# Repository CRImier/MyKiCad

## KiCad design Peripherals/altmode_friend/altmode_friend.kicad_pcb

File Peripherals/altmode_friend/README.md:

# Altmode Friend

This is a castellated module with a RP2040 and a FUSB302B on it.
The idea is to ship this as a together with a MicroPython
library that helps you talk USB-C - whether it's to get altmodes
out of a port, or provide some altmodes to a device,
all within a comfortable high-level environment.

Main three uses are DisplayPort, making PD sources, and PD sinks,
but you can most certainly find more than that.
Many RP2040 GPIOs are broken out, so that you can toggle hardware
in response to PD messages, i.e. signal muxes, or power management stuff.

Bring your own 3.3V. You don't need much else though!

The RP2040's USB port is broken out on the header. There's also
a voltage divider (with Zener fp) from VBUS. FUSB's VBUS is not wired up -
you might not want to do it either; due to some mfg weirdness,
it's a very sensitive pin, and not connecting it does not impact
FUSB's operation in any way. Two extra ADC pins are broken out,
but one of them is connected to BOOT with a resistor, so you need
to remove/shift the resistor marked "BT>" before you can use it.

VCONN is jumpered to on-module 3.3V by default. If emarkers don't work,
remove/shift the jumper and provide idk like 5V or whatever.
The jumper is marked as "<VC". It's important that you remove it.

The module is 2.54mm pitch, 6 pins on all sides. There's no footprint yet.
That said, all pins are on 2.54mm grid, can't be hard to add it wherever you want it.

This board can be used as a building block of your own board
or it can be used standalone, or copy-pasted as a heart of a new design,
Whichever path you take, I hope this board helps you.

## Notes

- Pin headers are arranged in a way that this board can be plugged into a breadboard.
- Signal names are silkscreened on the board's bottom layer.
- This board is untested and there's no guarantees of fitness.
- I recommend a stencil for assembling this board.

## Info

- Software: Kicad 6
- Version: 1
- PCB size: 18x18mm
- Layer count: 2

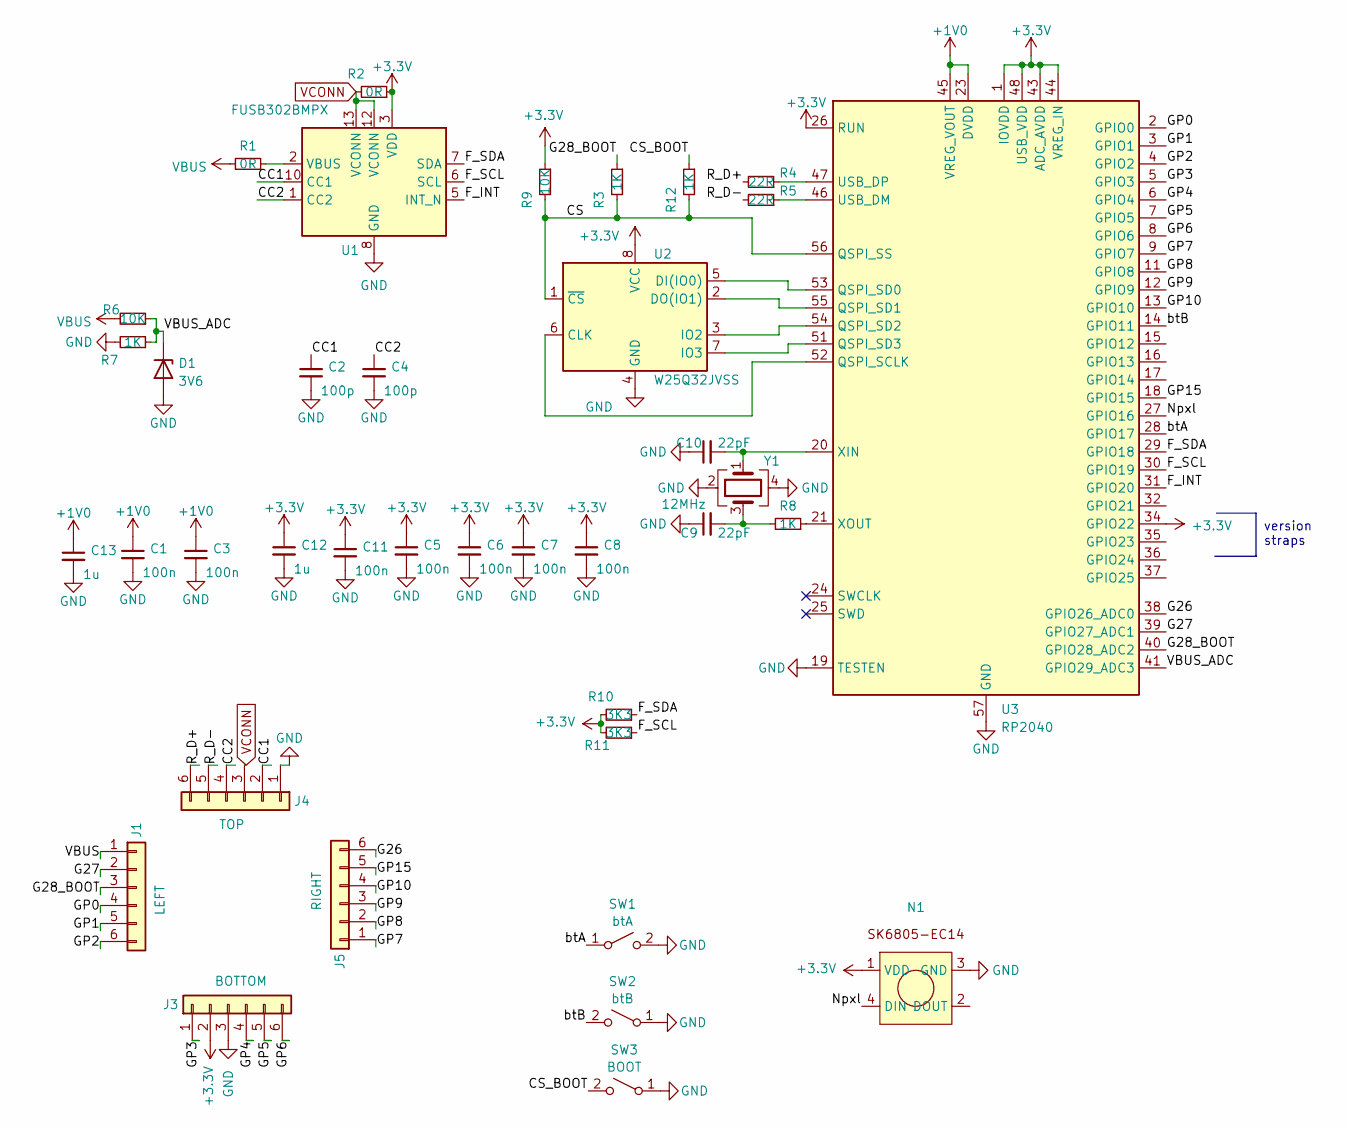
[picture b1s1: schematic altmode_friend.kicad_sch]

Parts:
C1, C3, C5, C6, C7, C8, C11: 100n; C_0402_1005Metric
C2, C4: 100p; C_0603_1608Metric
C9, C10: 22pF; C_0603_1608Metric
C12, C13: 1u; C_0402_1005Metric
D1: 3V6; D_0805_2012Metric
J1: LEFT; 6p_header
J3: BOTTOM; 6p_header
J4: TOP; 6p_header
J5: RIGHT; 6p_header
N1: SK6805-EC14
R1: 0R; R_0402_1005Metric
R2: 0R; R_0603_1608Metric
R3, R7, R8, R12: 1K; R_0402_1005Metric
R4, R5: 22R; R_0402_1005Metric
R6, R9: 10K; R_0402_1005Metric
R10, R11: 3K3; R_0402_1005Metric
SW1: btA; SW-SMD_4P-L2.8-W1.9-P1.20-LS3.0
SW2: btB; SW-SMD_4P-L2.8-W1.9-P1.20-LS3.0
SW3: BOOT; SW-SMD_4P-L2.8-W1.9-P1.20-LS3.0
U1: FUSB302BMPX; WQFN-14-1EP_2.5x2.5mm_P0.5mm_EP1.45x1.45mm
U2: W25Q32JVSS; DFN-8-1EP_3x2mm_P0.5mm_EP1.3x1.5mm
U3: RP2040; QFN-56-1EP_7x7mm_P0.4mm_EP3.2x3.2mm
Y1: 12MHz; Crystal_SMD_3225-4Pin_3.2x2.5mm

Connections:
+1V0: C1.1, C3.1, C13.1, U3.23 (DVDD), U3.45 (VREG_VOUT), U3.50 (DVDD)
+3.3V: C5.1, C6.1, C7.1, C8.1, C11.1, C12.1, J3.2, N1.1 (VDD), R2.1, R9.1, R10.2, R11.2, U1.3 (VDD), U1.4 (VDD), U2.8 (VCC), U3.1 (IOVDD), U3.10 (IOVDD), U3.22 (IOVDD), U3.26 (RUN), U3.33 (IOVDD), U3.34 (GPIO22), U3.42 (IOVDD), U3.43 (ADC_AVDD), U3.44 (VREG_IN), U3.48 (USB_VDD), U3.49 (IOVDD)
/CC1: C2.1, J4.2, U1.10 (CC1), U1.11 (CC1)
/CC2: C4.1, J4.4, U1.1 (CC2), U1.14 (CC2)
/CS: R3.2, R9.2, R12.2, U2.1 (~CS), U3.56 (QSPI_SS)
/CS_BOOT: R12.1, SW3.2 (B)
/F_INT: U1.5 (INT_N), U3.31 (GPIO20)
/F_SCL: R11.1, U1.6 (SCL), U3.30 (GPIO19)
/F_SDA: R10.1, U1.7 (SDA), U3.29 (GPIO18)
/G26: J5.6, U3.38 (GPIO26_ADC0)
/G27: J1.2, U3.39 (GPIO27_ADC1)
/G28_BOOT: J1.3, R3.1, U3.40 (GPIO28_ADC2)
/GP0: J1.4, U3.2 (GPIO0)
/GP1: J1.5, U3.3 (GPIO1)
/GP2: J1.6, U3.4 (GPIO2)
/GP3: J3.1, U3.5 (GPIO3)
/GP4: J3.4, U3.6 (GPIO4)
/GP5: J3.5, U3.7 (GPIO5)
/GP6: J3.6, U3.8 (GPIO6)
/GP7: J5.1, U3.9 (GPIO7)
/GP8: J5.2, U3.11 (GPIO8)
/GP9: J5.3, U3.12 (GPIO9)
/GP10: J5.4, U3.13 (GPIO10)
/GP15: J5.5, U3.18 (GPIO15)
/Npxl: N1.4 (DIN), U3.27 (GPIO16)
/R_D+: J4.6, R4.2
/R_D-: J4.5, R5.2
/VBUS_ADC: D1.1 (K), R6.1, R7.1, U3.41 (GPIO29_ADC3)
/btA: SW1.1 (A), U3.28 (GPIO17)
/btB: SW2.2 (B), U3.14 (GPIO11)
GND: C1.2, C2.2, C3.2, C4.2, C5.2, C6.2, C7.2, C8.2, C9.1, C10.1, C11.2, C12.2, C13.2, D1.2 (A), J3.3, J4.1, N1.3 (GND), R7.2, SW1.2 (B), SW2.1 (A), SW3.1 (A), U1.8 (GND), U1.9 (GND), U1.15 (GND), U2.4 (GND), U3.19 (TESTEN), U3.57 (GND), Y1.2, Y1.4
unnamed: C9.2, R8.2, Y1.3
unnamed: R1.1, U1.2 (VBUS)
unnamed: U2.6 (CLK), U3.52 (QSPI_SCLK)
unnamed: U2.5 (DI(IO0)), U3.53 (QSPI_SD0)
unnamed: U2.2 (DO(IO1)), U3.55 (QSPI_SD1)
unnamed: U2.3 (IO2), U3.54 (QSPI_SD2)
unnamed: U2.7 (IO3), U3.51 (QSPI_SD3)
unnamed: R5.1, U3.46 (USB_DM)
unnamed: R4.1, U3.47 (USB_DP)
unnamed: C10.2, U3.20 (XIN), Y1.1
unnamed: R8.1, U3.21 (XOUT)
VBUS: J1.1, R1.2, R6.2
VCONN: J4.3, R2.2, U1.12 (VCONN), U1.13 (VCONN)

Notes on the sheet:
version straps

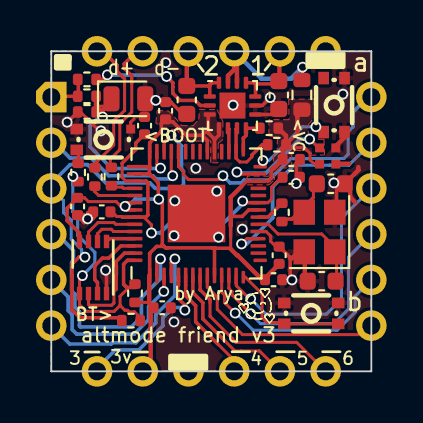
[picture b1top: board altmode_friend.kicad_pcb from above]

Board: 2 copper layers, 17.8 x 17.8 mm, 38 parts (0 on the bottom side), 44 nets.

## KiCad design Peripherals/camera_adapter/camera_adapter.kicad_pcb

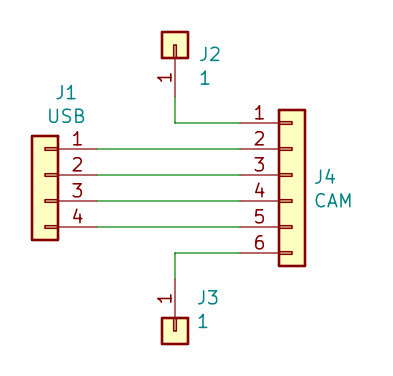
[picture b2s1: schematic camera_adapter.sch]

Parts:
J1: USB; PinHeader_1x04_P2.00mm_Vertical
J2, J3: 1; PinHeader_1x01_P2.00mm_Vertical
J4: CAM; JST_SH_BM06B-SRSS-TB_1x06-1MP_P1.00mm_Vertical

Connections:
unnamed: J1.1, J4.2
unnamed: J1.2, J4.3
unnamed: J1.3, J4.4
unnamed: J1.4, J4.5
unnamed: J2.1, J4.1
unnamed: J3.1, J4.6

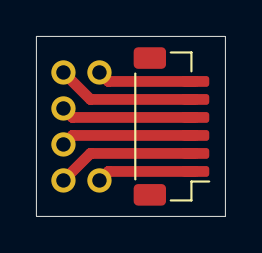
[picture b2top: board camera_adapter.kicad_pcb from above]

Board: 2 copper layers, 10.5 x 10.0 mm, 4 parts (0 on the bottom side), 6 nets.

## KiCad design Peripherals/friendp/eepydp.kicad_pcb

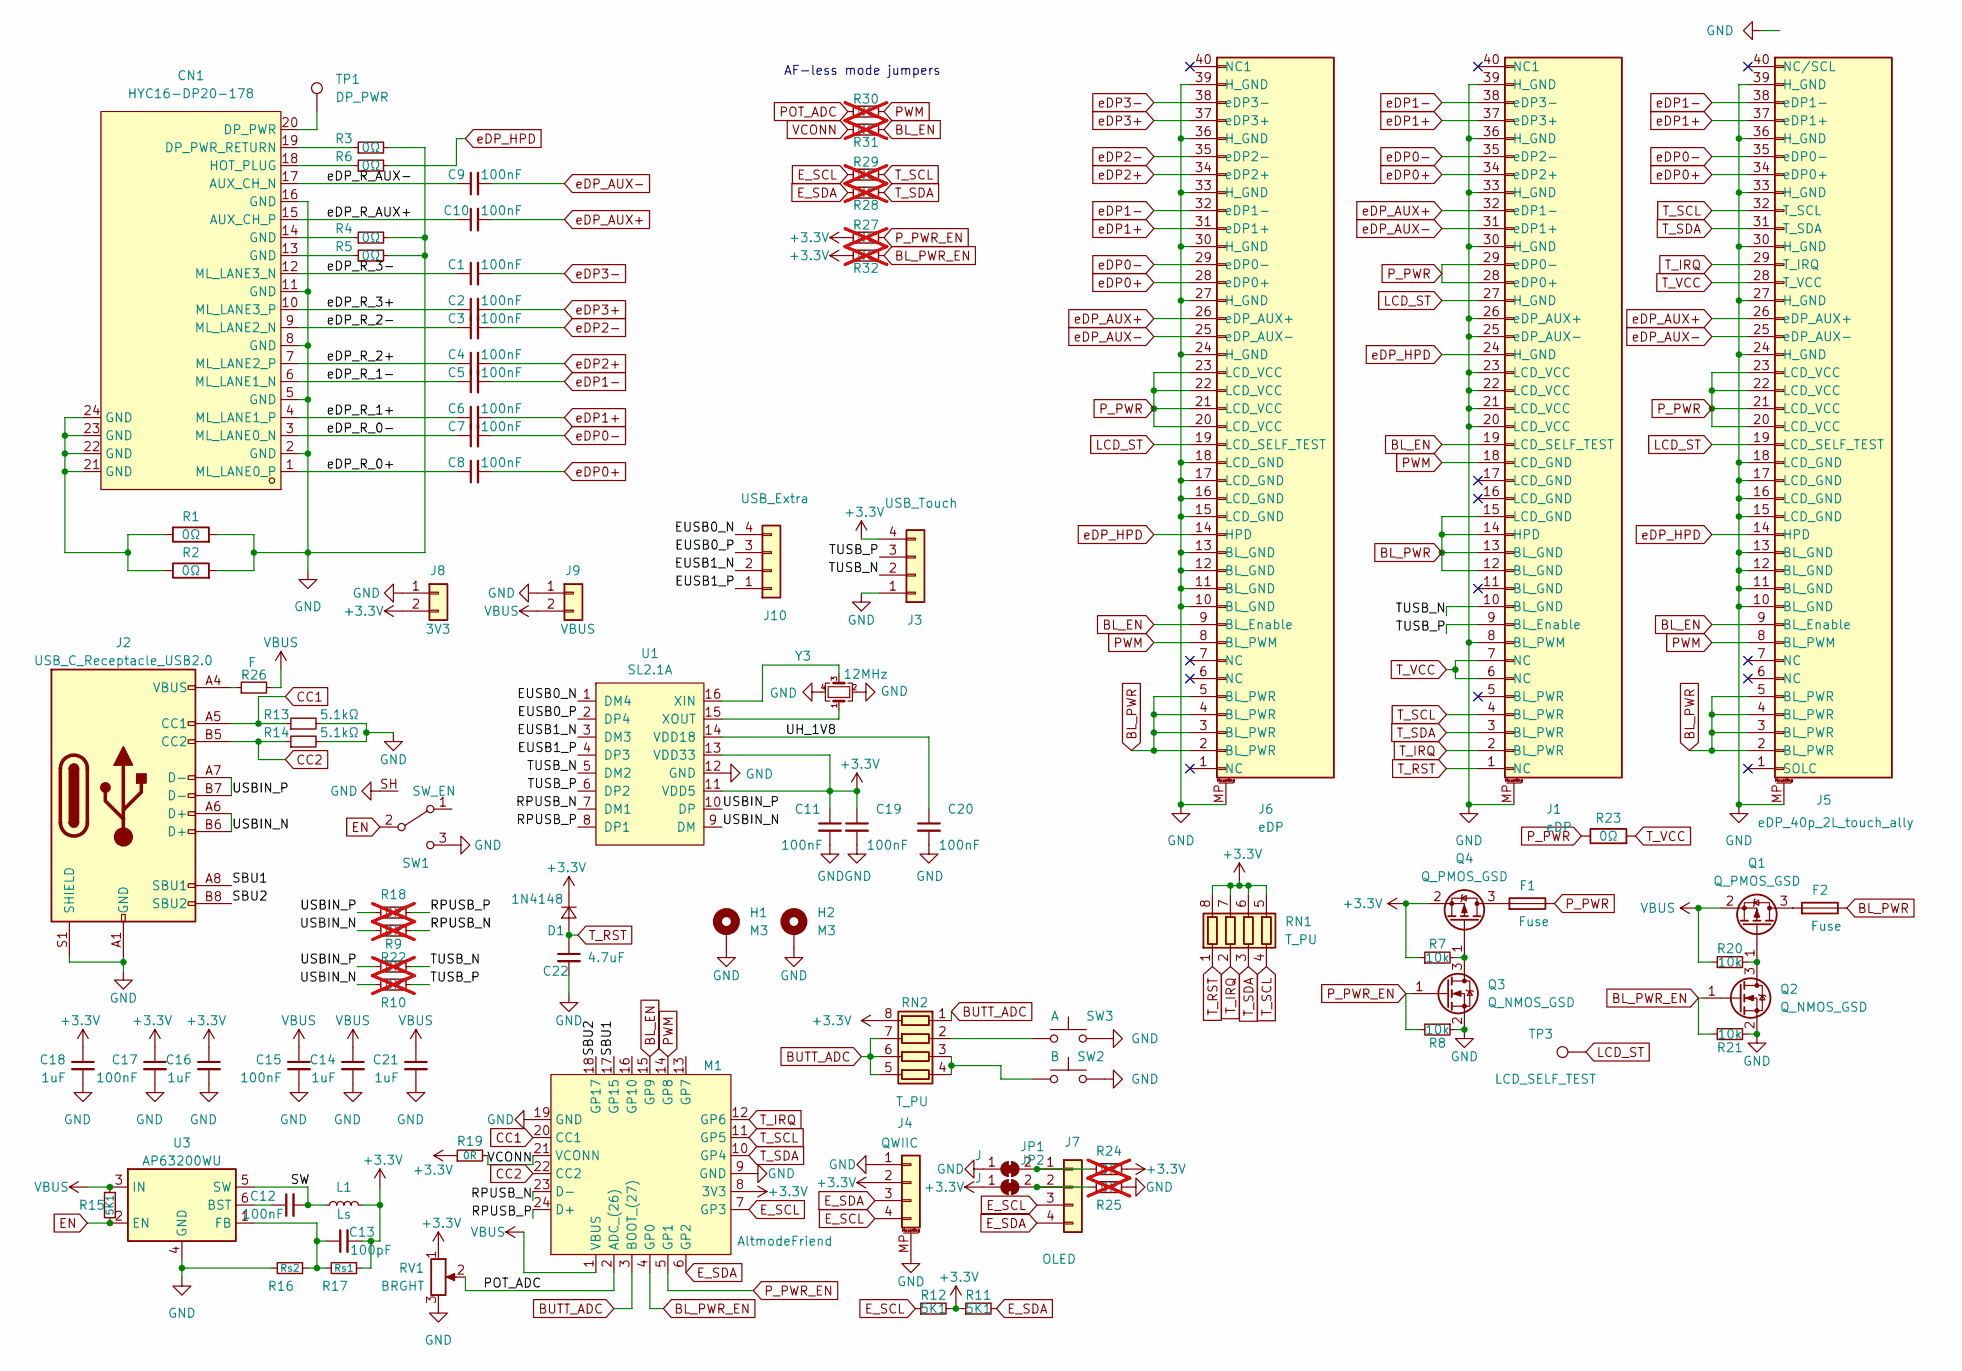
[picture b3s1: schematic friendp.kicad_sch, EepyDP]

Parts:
C1, C2, C3, C4, C5, C6, C7, C8, C9, C10: 100nF; C_0402_1005Metric
C11, C12, C17, C19, C20: 100nF; C_0603_1608Metric
C13: 100pF; C_0603_1608Metric
C14, C16, C18, C21: 1uF; C_0805_2012Metric
C15: 100nF; C_0805_2012Metric
C22: 4.7uF; C_0805_2012Metric
CN1: HYC16-DP20-178; DP-SMD_HYC16-DP20-178; LCSC Part C711350
D1: 1N4148; D_SOD-123F
F1, F2: Fuse; Fuse_0805_2012Metric
H1, H2: M3; MountingHole_3.2mm_M3_Pad
J1, J6: eDP; TE_4-1734839-0_1x40-1MP_P0.5mm_Horizontal
J2: USB_C_Receptacle_USB2.0; USB_C_Receptacle_HRO_TYPE-C-31-M-12
J3: USB_Touch; PinHeader_1x04_P2.54mm_Vertical
J4: QWIIC; JST_SH_SM04B-SRSS-TB_1x04-1MP_P1.00mm_Horizontal
J5: eDP_40p_2L_touch_ally; TE_4-1734839-0_1x40-1MP_P0.5mm_Horizontal
J7: OLED; PinHeader_1x04_P2.54mm_Vertical
J8: 3V3; PinHeader_1x02_P2.54mm_Vertical
J9: VBUS; PinHeader_1x02_P2.54mm_Vertical
J10: USB_Extra; PinHeader_1x04_P2.54mm_Vertical
JP1, JP2: J; R_0603_1608Metric_Jumper
L1: Ls; L_Bourns-SRN4018
M1: AltmodeFriend; altmode_friend
Q1, Q4: Q_PMOS_GSD; SOT-23
Q2, Q3: Q_NMOS_GSD; SOT-23
R1, R2: 0Ω; R_0603_1608Metric
R3, R4, R5, R6, R23: 0Ω; R_0603_1608Metric_Jumper
R7, R8, R20, R21: 10k; R_0603_1608Metric
R9, R10, R18, R22, R24, R25: 0R; R_0603_1608Metric; not fitted
R11, R12, R15: 5K1; R_0603_1608Metric
R13, R14: 5.1kΩ; R_0603_1608Metric
R16: Rs2; R_0603_1608Metric
R17: Rs1; R_0603_1608Metric
R19: 0R; R_0603_1608Metric_Jumper
R26: F; R_0805_2012Metric
R27, R28, R29, R30, R31, R32: NC; R_0603_1608Metric; not fitted
RN1, RN2: T_PU; R_Array_Convex_4x0603
RV1: BRGHT; RES-ADJ-TH_VZ067TL1B202
SW1: SW_EN; SW_SPDT_PCM12_SH
SW2: B; SW_SPST_FSMSM
SW3: A; SW_SPST_FSMSM
TP1: DP_PWR; TestPoint_Pad_1.0x1.0mm
TP3: LCD_SELF_TEST; TestPoint_Pad_1.0x1.0mm
U1: SL2.1A; SO-16_3.9x9.9mm_P1.27mm
U3: AP63200WU; TSOT-23-6
Y3: 12MHz; Crystal_SMD_3225-4Pin_3.2x2.5mm

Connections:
+3.3V: C11.1, C13.2, C16.1, C17.1, C18.1, C19.1, D1.1 (K), J3.4, J4.2, J8.2, JP2.1 (A), L1.2, M1.8 (3V3), Q4.2 (S), R7.1, R11.1, R12.2, R17.1, R19.1, R24.1, R27.1, R32.1, RN1.5 (R4.2), RN1.6 (R3.2), RN1.7 (R2.2), RN1.8 (R1.2), RN2.8 (R1.2), RV1.1, U1.11 (VDD5), U1.13 (VDD33)
/EUSB0_N: J10.4, U1.1 (DM4)
/EUSB0_P: J10.3, U1.2 (DP4)
/EUSB1_N: J10.2, U1.3 (DM3)
/EUSB1_P: J10.1, U1.4 (DP3)
/RPUSB_N: M1.23 (D-), R22.1, U1.7 (DM1)
/RPUSB_P: M1.24 (D+), R18.1, U1.8 (DP1)
/SBU1: J2.A8 (SBU1), M1.17 (GP15)
/SBU2: J2.B8 (SBU2), M1.18 (GP17)
/SW: C12.2, L1.1, U3.5 (SW)
/TUSB_N: J1.10 (BL_GND), J3.2, R9.1, U1.5 (DM2)
/TUSB_P: J1.9 (BL_Enable), J3.3, R10.1, U1.6 (DP2)
/UH_1V8: C20.1, U1.14 (VDD18)
/USBIN_N: J2.A6 (D+), J2.B6 (D+), R10.2, R22.2, U1.9 (DM)
/USBIN_P: J2.A7 (D-), J2.B7 (D-), R9.2, R18.2, U1.10 (DP)
/eDP_R_0+: C8.1, CN1.1 (ML_LANE0_P)
/eDP_R_0-: C7.1, CN1.3 (ML_LANE0_N)
/eDP_R_1+: C6.1, CN1.4 (ML_LANE1_P)
/eDP_R_1-: C5.1, CN1.6 (ML_LANE1_N)
/eDP_R_2+: C4.1, CN1.7 (ML_LANE2_P)
/eDP_R_2-: C3.1, CN1.9 (ML_LANE2_N)
/eDP_R_3+: C2.1, CN1.10 (ML_LANE3_P)
/eDP_R_3-: C1.1, CN1.12 (ML_LANE3_N)
/eDP_R_AUX+: C10.1, CN1.15 (AUX_CH_P)
/eDP_R_AUX-: C9.1, CN1.17 (AUX_CH_N)
BL_EN: J1.19 (LCD_SELF_TEST), J5.9 (BL_Enable), J6.9 (BL_Enable), M1.15 (GP9), R31.2
BL_PWR: F2.1, J1.12 (BL_GND), J1.13 (BL_GND), J1.14 (HPD), J1.15 (LCD_GND), J5.2 (BL_PWR), J5.3 (BL_PWR), J5.4 (BL_PWR), J5.5 (BL_PWR), J6.2 (BL_PWR), J6.3 (BL_PWR), J6.4 (BL_PWR), J6.5 (BL_PWR)
BL_PWR_EN: M1.4 (GP0), Q2.1 (G), R21.2, R32.2
BUTT_ADC: M1.3 (BOOT_(27)), RN2.1 (R1.1), RN2.5 (R4.2), RN2.6 (R3.2), RN2.7 (R2.2)
CC1: J2.A5 (CC1), M1.20 (CC1), R13.1
CC2: J2.B5 (CC2), M1.22 (CC2), R14.1
EN: R15.1, SW1.2 (B), U3.2 (EN)
E_SCL: J4.4, J7.3, M1.7 (GP3), R12.1, R29.1
E_SDA: J4.3, J7.4, M1.6 (GP2), R11.2, R28.1
GND: C11.2, C14.2, C15.2, C16.2, C17.2, C18.2, C19.2, C20.2, C21.2, C22.2, CN1.2 (GND), CN1.5 (GND), CN1.8 (GND), CN1.11 (GND), CN1.16 (GND), H1.1, H2.1, J1.8 (BL_PWM), J1.20 (LCD_VCC), J1.21 (LCD_VCC), J1.22 (LCD_VCC), J1.23 (LCD_VCC), J1.25 (eDP_AUX-), J1.26 (eDP_AUX+), J1.30 (H_GND), J1.33 (H_GND), J1.36 (H_GND), J1.39 (H_GND), J1.MP, J2.A1 (GND), J2.A12 (GND), J2.B1 (GND), J2.B12 (GND), J2.S1 (SHIELD), J3.1, J4.1, J4.MP (MountPin), J5.10 (BL_GND), J5.11 (BL_GND), J5.12 (BL_GND), J5.13 (BL_GND), J5.15 (LCD_GND), J5.16 (LCD_GND), J5.17 (LCD_GND), J5.18 (LCD_GND), J5.24 (H_GND), J5.27 (H_GND), J5.30 (H_GND), J5.33 (H_GND), J5.36 (H_GND), J5.39 (H_GND), J5.MP, J6.10 (BL_GND), J6.11 (BL_GND), J6.12 (BL_GND), J6.13 (BL_GND), J6.15 (LCD_GND), J6.16 (LCD_GND), J6.17 (LCD_GND), J6.18 (LCD_GND), J6.24 (H_GND), J6.27 (H_GND), J6.30 (H_GND), J6.33 (H_GND), J6.36 (H_GND), J6.39 (H_GND), J6.MP, J8.1, J9.1, JP1.1 (A), M1.9 (GND), M1.19 (GND), Q2.2 (S), Q3.2 (S), R1.2, R2.2, R3.2, R4.2, R5.2, R8.1, R13.2, R14.2, R16.2, R21.1, R25.1, RV1.3, SW1.3 (C), SW1.SH, SW2.1, SW3.1, U1.12 (GND), U3.4 (GND), Y3.2, Y3.4
LCD_ST: J1.27 (H_GND), J5.19 (LCD_SELF_TEST), J6.19 (LCD_SELF_TEST), TP3.1
unnamed: CN1.20 (DP_PWR), TP1.1
unnamed: CN1.19 (DP_PWR_RETURN), R3.1
unnamed: CN1.13 (GND), R5.1
unnamed: CN1.14 (GND), R4.1
unnamed: CN1.21 (GND), CN1.22 (GND), CN1.23 (GND), CN1.24 (GND), R1.1, R2.1
unnamed: CN1.18 (HOT_PLUG), R6.1
unnamed: J2.A4 (VBUS), J2.A9 (VBUS), J2.B4 (VBUS), J2.B9 (VBUS), R26.1
unnamed: J7.1, JP1.2 (B), R24.2
unnamed: J7.2, JP2.2 (B), R25.2
unnamed: F2.2, Q1.3 (D)
unnamed: Q1.1 (G), Q2.3 (D), R20.2
unnamed: Q3.3 (D), Q4.1 (G), R7.2
unnamed: F1.2, Q4.3 (D)
unnamed: RN2.2 (R2.1), SW3.2
unnamed: RN2.3 (R3.1), RN2.4 (R4.1), SW2.2
unnamed: U1.16 (XIN), Y3.3
unnamed: U1.15 (XOUT), Y3.1
unnamed: C12.1, U3.6 (BST)
unnamed: C13.1, R16.1, R17.2, U3.1 (FB)
POT_ADC: M1.2 (ADC_(26)), R30.1, RV1.2
PWM: J1.18 (LCD_GND), J5.8 (BL_PWM), J6.8 (BL_PWM), M1.14 (GP8), R30.2
P_PWR: F1.1, J1.28 (eDP0+), J1.29 (eDP0-), J5.20 (LCD_VCC), J5.21 (LCD_VCC), J5.22 (LCD_VCC), J5.23 (LCD_VCC), J6.20 (LCD_VCC), J6.21 (LCD_VCC), J6.22 (LCD_VCC), J6.23 (LCD_VCC), R23.1
P_PWR_EN: M1.5 (GP1), Q3.1 (G), R8.2, R27.2
T_IRQ: J1.2 (BL_PWR), J5.29 (T_IRQ), M1.12 (GP6), RN1.2 (R2.1)
T_RST: C22.1, D1.2 (A), J1.1 (NC), RN1.1 (R1.1)
T_SCL: J1.4 (BL_PWR), J5.32 (T_SCL), M1.11 (GP5), R29.2, RN1.4 (R4.1)
T_SDA: J1.3 (BL_PWR), J5.31 (T_SDA), M1.10 (GP4), R28.2, RN1.3 (R3.1)
T_VCC: J1.6 (NC), J1.7 (NC), J5.28 (T_VCC), R23.2
VBUS: C14.1, C15.1, C21.1, J9.2, M1.1 (VBUS), Q1.2 (S), R15.2, R20.1, R26.2, U3.3 (IN)
VCONN: M1.21 (VCONN), R19.2, R31.1
eDP0+: C8.2, J1.34 (eDP2+), J5.34 (eDP0+), J6.28 (eDP0+)
eDP0-: C7.2, J1.35 (eDP2-), J5.35 (eDP0-), J6.29 (eDP0-)
eDP1+: C6.2, J1.37 (eDP3+), J5.37 (eDP1+), J6.31 (eDP1+)
eDP1-: C5.2, J1.38 (eDP3-), J5.38 (eDP1-), J6.32 (eDP1-)
eDP2+: C4.2, J6.34 (eDP2+)
eDP2-: C3.2, J6.35 (eDP2-)
eDP3+: C2.2, J6.37 (eDP3+)
eDP3-: C1.2, J6.38 (eDP3-)
eDP_AUX+: C10.2, J1.32 (eDP1-), J5.26 (eDP_AUX+), J6.26 (eDP_AUX+)
eDP_AUX-: C9.2, J1.31 (eDP1+), J5.25 (eDP_AUX-), J6.25 (eDP_AUX-)
eDP_HPD: J1.24 (H_GND), J5.14 (HPD), J6.14 (HPD), R6.2

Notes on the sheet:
AF-less mode jumpers

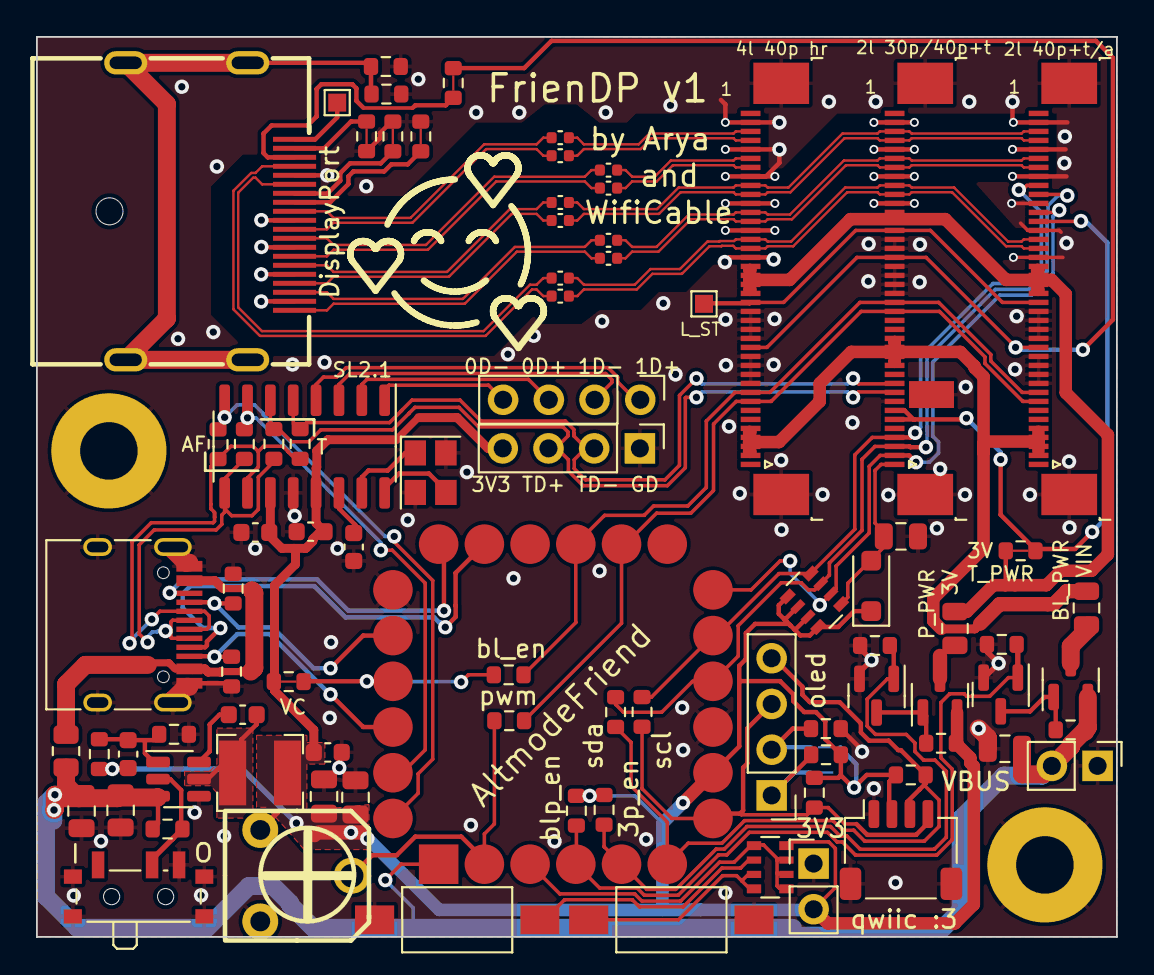
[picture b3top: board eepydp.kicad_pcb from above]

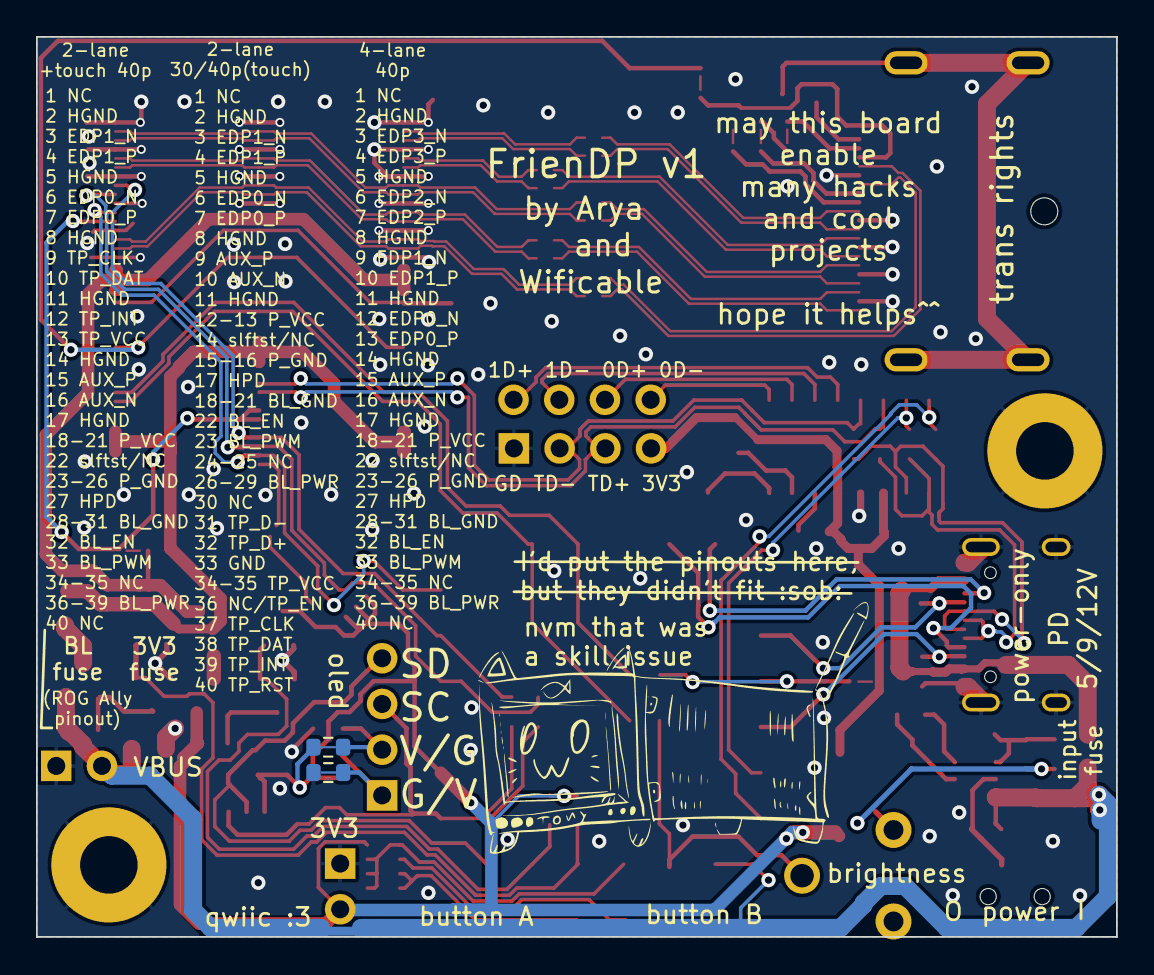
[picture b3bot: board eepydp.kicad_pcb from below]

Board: 4 copper layers, 60.0 x 50.0 mm, 89 parts (2 on the bottom side), 77 nets.

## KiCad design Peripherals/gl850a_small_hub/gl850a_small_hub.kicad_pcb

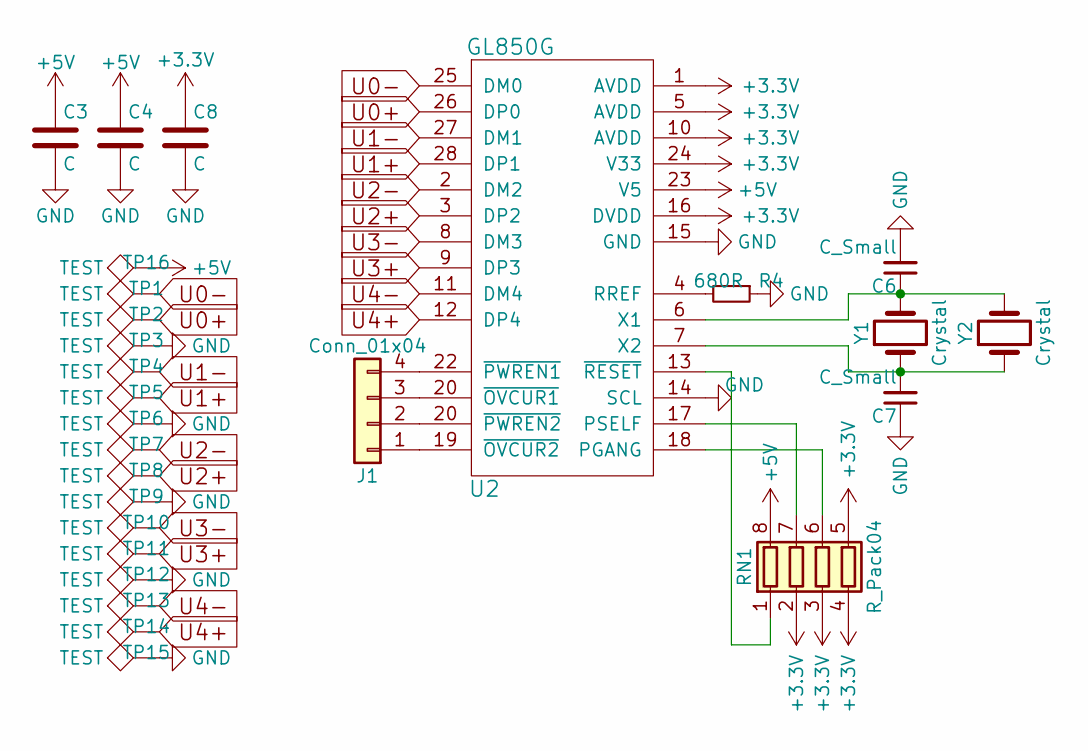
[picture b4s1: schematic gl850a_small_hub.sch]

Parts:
C3, C8: C; C_0603
C4: C; C_0805
C6, C7: C_Small; C_0603
J1: Conn_01x04; Pin_Header_Straight_1x04_Pitch1.27mm
R4: 680R; R_0603
RN1: R_Pack04; R_Array_Convex_4x0603
TP1, TP2, TP3, TP4, TP5, TP6, TP7, TP8, TP9, TP10, TP11, TP12, TP13, TP14, TP15, TP16: TEST; StrainReliefPoint
U2: GL850G; SSOP-28_3.9x9.9mm_Pitch0.635mm
Y1: Crystal; Crystal_SMD_3215-2pin_3.2x1.5mm
Y2: Crystal; Crystal_HC49-U_Vertical

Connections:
+3V3: C8.1, RN1.2 (R2.1), RN1.3 (R3.1), RN1.4 (R4.1), RN1.5 (R4.2), U2.1 (AVDD), U2.5 (AVDD), U2.10 (AVDD), U2.16 (DVDD), U2.24 (V33)
+5V: C3.1, C4.1, RN1.8 (R1.2), TP16.1, U2.23 (V5)
GND: C3.2, C4.2, C6.2, C7.1, C8.2, R4.1, TP3.1, TP6.1, TP9.1, TP12.1, TP15.1, U2.14 (SCL), U2.15 (GND)
unnamed: C6.1, U2.6 (X1), Y1.2, Y2.2
unnamed: C7.2, U2.7 (X2), Y1.1, Y2.1
unnamed: J1.1, U2.19 (~OVCUR2)
unnamed: J1.2, J1.3, U2.20 (~OVCUR1)
unnamed: J1.4, U2.22 (~PWREN1)
unnamed: R4.2, U2.4 (RREF)
unnamed: RN1.1 (R1.1), U2.13 (~RESET)
unnamed: RN1.6 (R3.2), U2.18 (PGANG)
unnamed: RN1.7 (R2.2), U2.17 (PSELF)
U0+: TP2.1, U2.26 (DP0)
U0-: TP1.1, U2.25 (DM0)
U1+: TP5.1, U2.28 (DP1)
U1-: TP4.1, U2.27 (DM1)
U2+: TP8.1, U2.3 (DP2)
U2-: TP7.1, U2.2 (DM2)
U3+: TP11.1, U2.9 (DP3)
U3-: TP10.1, U2.8 (DM3)
U4+: TP14.1, U2.12 (DP4)
U4-: TP13.1, U2.11 (DM4)

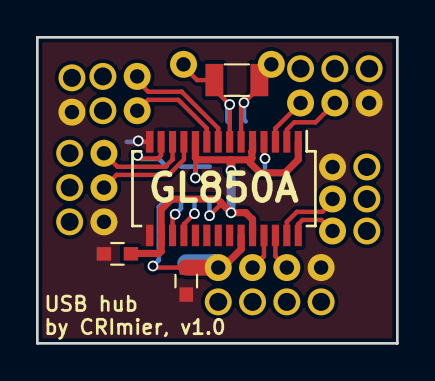
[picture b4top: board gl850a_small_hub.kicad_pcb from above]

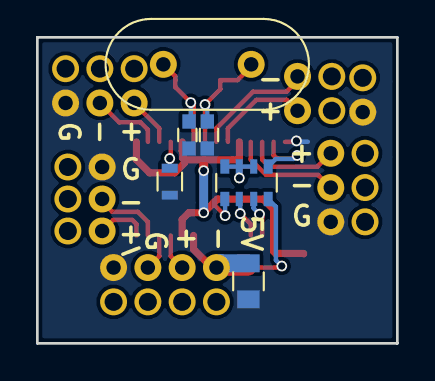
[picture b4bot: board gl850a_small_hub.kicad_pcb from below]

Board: 2 copper layers, 20.0 x 17.0 mm, 26 parts (6 on the bottom side), 19 nets.

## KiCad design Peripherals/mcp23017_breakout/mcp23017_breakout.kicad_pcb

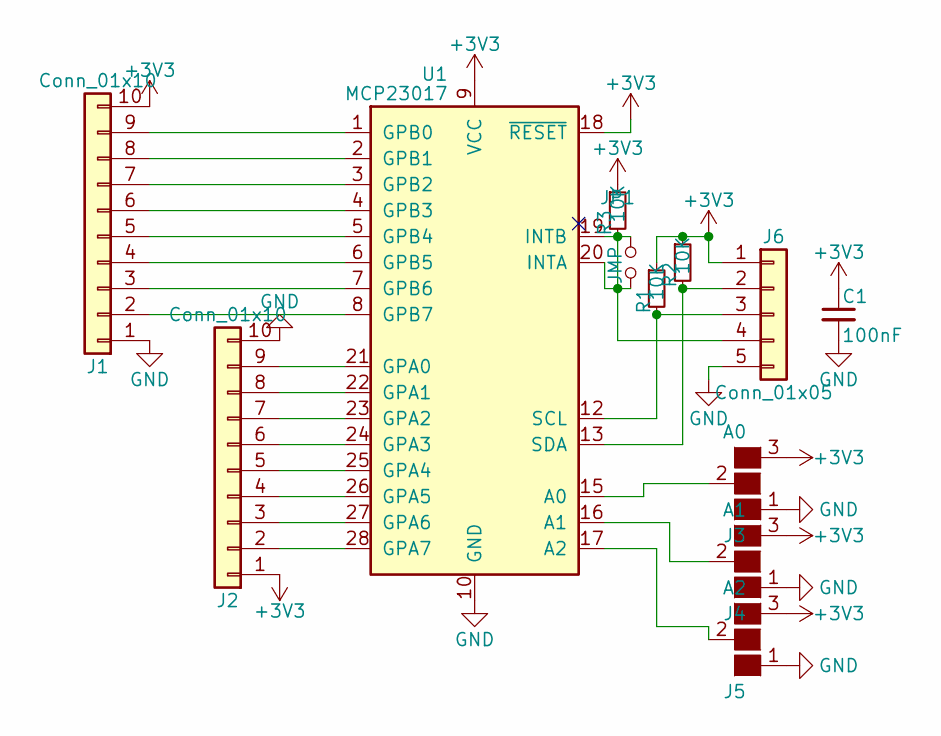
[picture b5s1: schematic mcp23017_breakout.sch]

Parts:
C1: 100nF; C_0805_HandSoldering
J1, J2: Conn_01x10; Pin_Header_Straight_1x10_Pitch2.54mm
J3: A0; GS3
J4: A1; GS3
J5: A2; GS3
J6: Conn_01x05; Pin_Header_Straight_1x05_Pitch2.54mm
JP1: JMP; GS2
R1, R2, R3: 10K; R_0805_HandSoldering
U1: MCP23017; SSOP-28_5.3x10.2mm_Pitch0.65mm

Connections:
+3V3: C1.1, J1.10, J2.1, J3.3 (G3), J4.3 (G3), J5.3 (G3), J6.1, R1.1, R2.1, R3.1, U1.9 (VCC), U1.18 (~RESET)
GND: C1.2, J1.1, J2.10, J3.1 (G1), J4.1 (G1), J5.1 (G1), J6.5, U1.10 (GND)
unnamed: J1.2, U1.8 (GPB7)
unnamed: J1.3, U1.7 (GPB6)
unnamed: J1.4, U1.6 (GPB5)
unnamed: J1.5, U1.5 (GPB4)
unnamed: J1.6, U1.4 (GPB3)
unnamed: J1.7, U1.3 (GPB2)
unnamed: J1.8, U1.2 (GPB1)
unnamed: J1.9, U1.1 (GPB0)
unnamed: J2.2, U1.28 (GPA7)
unnamed: J2.3, U1.27 (GPA6)
unnamed: J2.4, U1.26 (GPA5)
unnamed: J2.5, U1.25 (GPA4)
unnamed: J2.6, U1.24 (GPA3)
unnamed: J2.7, U1.23 (GPA2)
unnamed: J2.8, U1.22 (GPA1)
unnamed: J2.9, U1.21 (GPA0)
unnamed: J3.2 (G2), U1.15 (A0)
unnamed: J4.2 (G2), U1.16 (A1)
unnamed: J5.2 (G2), U1.17 (A2)
unnamed: J6.2, R2.2, U1.13 (SDA)
unnamed: J6.3, R1.2, U1.12 (SCL)
unnamed: J6.4, JP1.1, JP1.2, R3.2, U1.19 (INTB), U1.20 (INTA)

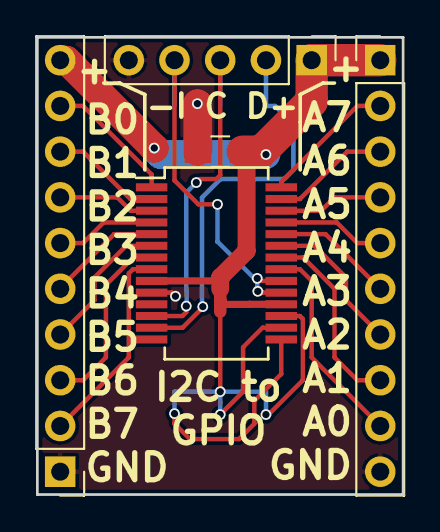
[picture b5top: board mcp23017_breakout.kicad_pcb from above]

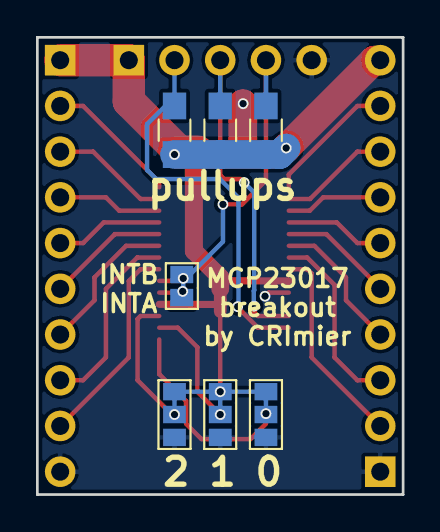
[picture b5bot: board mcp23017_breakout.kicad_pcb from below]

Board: 2 copper layers, 20.3 x 25.4 mm, 12 parts (7 on the bottom side), 24 nets.

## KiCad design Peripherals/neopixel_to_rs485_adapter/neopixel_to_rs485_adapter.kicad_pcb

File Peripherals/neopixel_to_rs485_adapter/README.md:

# Neopixel to RS485 adapter for Neopixel extension

This is a MAX485-based PCB to transfer Neopixel (WS2812) signal over large distances.
It transforms the 800KHz signal into a differential one, so it is more resistant to noise
and allows you to send the LED signal over longer distances, or next to some power wires.
Otherwise, with long runs, the WS2812 signal gets noisy and some LEDs can switch randomly
every time you send data to the LED strip.

You can attach the usual 3-pin LED strip connector end to one end of this board. The other end
has 3 pins - -, + and GND. It's best if you connect something like a twisted pair cable to these,
a pair out of an Ethernet cable will do well. It's recommended that you also add a GND wire and
connect it on both sides - the board might not work otherwise, or MAX485 inputs might die.
You can use an Ethernet cable, use one of the pairs for communications, and all of the other wires for GND.

Both ends of the board have extra holes that you put the wires through before soldering them,
so that there's less chance for the wires to break off at the solder joint. So, make use of those holes!

The board works off 5V. It will probably not accept 3.3V signal without level shifting,
not that I want to discourage you from trying.

On the bottom side of the board has a footprint for a 6-pin ESD diode package. It's useful
to prevent destroying the MAX485, but is not a guarantee that it'll stay alive.

Pin headers are arranged in a way that this board might be pluggable into a breadboard...
if you need that for some reason.
Signal names are silkscreened on the board's bottom layer.

This specific board is untested and there's no guarantees of fitness, but the concept itself is tested and shown to be working.

- PCB size: 32*8.5mm
- Layer count: 2

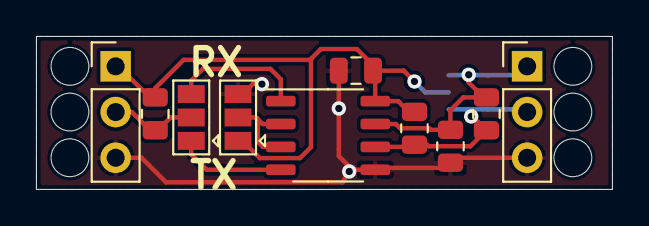
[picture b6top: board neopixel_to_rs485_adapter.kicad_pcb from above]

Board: 2 copper layers, 32.0 x 8.5 mm, 17 parts (1 on the bottom side), 8 nets.

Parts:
C1: 100nF; C_0805_2012Metric
H3, H3#2, H3#3, H3#4, H3#5, H3#6: MountingHole; wire_hole
J1: NEO; PinHeader_1x03_P2.54mm_Vertical
J2: RS485; PinHeader_1x03_P2.54mm_Vertical
JP1, JP2: DIR; SolderJumper-3_P1.3mm_Open_Pad1.0x1.5mm
R1, R3, R4: RSP; R_0805_2012Metric
R2: 120; R_0805_2012Metric
U1: MAX485E; SOP-8_3.9x4.9mm_P1.27mm
U2: SRV05-4; SOT-23-6

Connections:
/A: J2.2, R2.2, R3.1, U1.6, U2.3, U2.4
/B: J2.1, R1.2, R2.1, U1.7, U2.1, U2.6
CH: J1.2, JP1.2, R4.2
GND: C1.2, J1.3, J2.3, JP2.3, R1.1, U1.5, U2.2
IN: JP1.1, U1.4
MO: JP2.2, U1.2, U1.3
OUT: JP1.3, U1.1
VCC: C1.1, J1.1, JP2.1, R3.2, R4.1, U1.8, U2.5

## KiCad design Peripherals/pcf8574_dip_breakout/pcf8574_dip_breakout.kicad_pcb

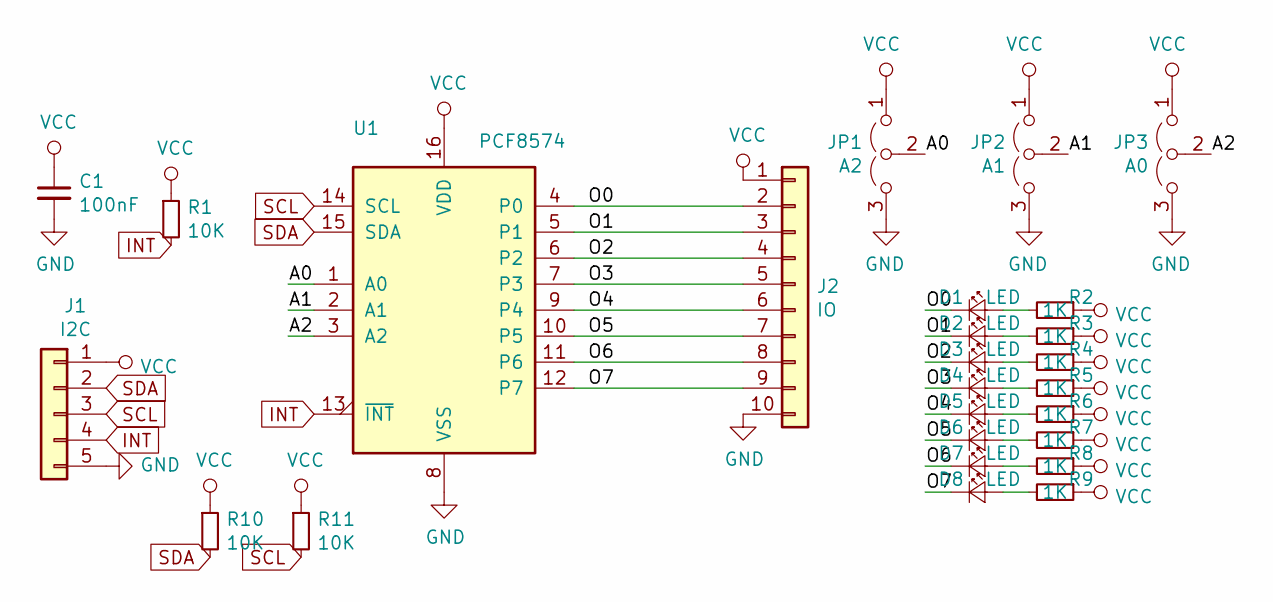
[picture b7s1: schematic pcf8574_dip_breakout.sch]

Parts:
C1: 100nF; C_0805_100nF_HandSoldering
D1, D2, D3, D4, D5, D6, D7, D8: LED; LED_0805_2012Metric_Pad1.15x1.40mm_HandSolder
J1: I2C; PinHeader_1x05_P2.54mm_Vertical
J2: IO; PinHeader_1x10_P2.54mm_Vertical
JP1: A2; GS3_SMALL
JP2: A1; GS3_SMALL
JP3: A0; GS3_SMALL
R1, R10, R11: 10K; R_0805_10K_HandSoldering
R2, R3, R4, R5, R6, R7, R8, R9: 1K; R_0805_10K_HandSoldering
U1: PCF8574; DIP-16_W7.62mm_LongPads

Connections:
/A0: JP1.2 (C), U1.1 (A0)
/A1: JP2.2 (C), U1.2 (A1)
/A2: JP3.2 (C), U1.3 (A2)
/O0: D1.1 (K), J2.2, U1.4 (P0)
/O1: D2.1 (K), J2.3, U1.5 (P1)
/O2: D3.1 (K), J2.4, U1.6 (P2)
/O3: D4.1 (K), J2.5, U1.7 (P3)
/O4: D5.1 (K), J2.6, U1.9 (P4)
/O5: D6.1 (K), J2.7, U1.10 (P5)
/O6: D7.1 (K), J2.8, U1.11 (P6)
/O7: D8.1 (K), J2.9, U1.12 (P7)
GND: C1.2, J1.5, J2.10, JP1.3 (B), JP2.3 (B), JP3.3 (B), U1.8 (VSS)
INT: J1.4, R1.2, U1.13 (~INT~)
unnamed: D1.2 (A), R2.2
unnamed: D2.2 (A), R3.2
unnamed: D3.2 (A), R4.2
unnamed: D4.2 (A), R5.2
unnamed: D5.2 (A), R6.2
unnamed: D6.2 (A), R7.2
unnamed: D7.2 (A), R8.2
unnamed: D8.2 (A), R9.2
SCL: J1.3, R11.2, U1.14 (SCL)
SDA: J1.2, R10.2, U1.15 (SDA)
VCC: C1.1, J1.1, J2.1, JP1.1 (A), JP2.1 (A), JP3.1 (A), R1.1, R2.1, R3.1, R4.1, R5.1, R6.1, R7.1, R8.1, R9.1, R10.1, R11.1, U1.16 (VDD)

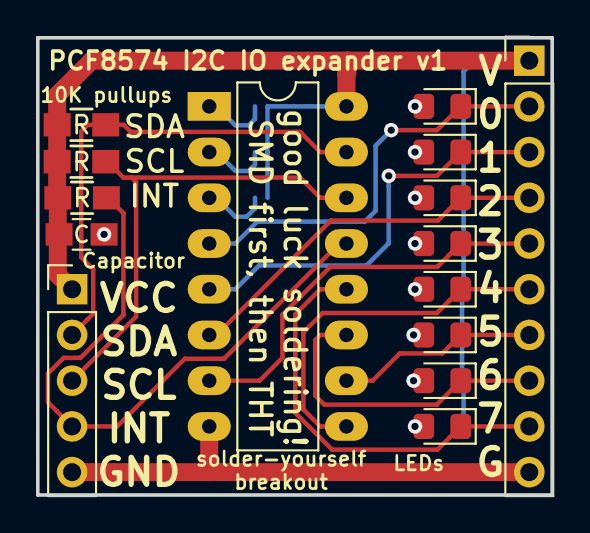
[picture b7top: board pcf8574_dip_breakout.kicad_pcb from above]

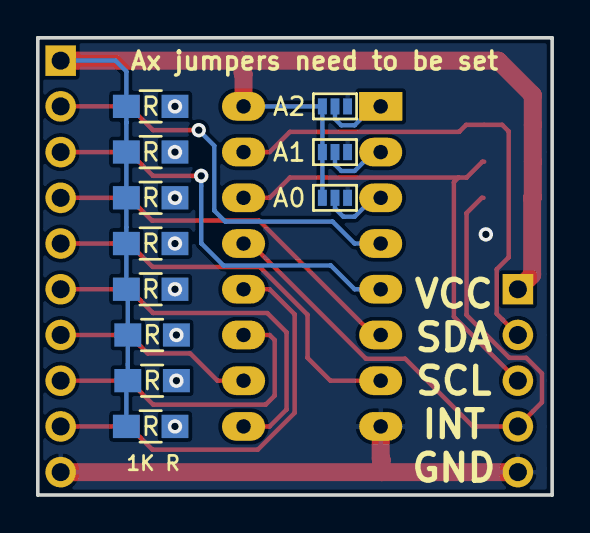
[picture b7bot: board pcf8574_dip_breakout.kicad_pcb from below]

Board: 2 copper layers, 28.6 x 25.4 mm, 26 parts (11 on the bottom side), 24 nets.
